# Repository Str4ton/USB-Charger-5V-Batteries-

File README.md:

# USB-Charger-5V-Batteries
A USB Charger for 5V Li-Ion batteries. It is designed to charge from a usb port, or something that will give 5V, 0.5A.

The circuit has a few protection circuits:
- A current limiter circuit so that the battery charges safely.
- A reverse polarity protection in case the battery is plugged in backwards that will not allow the circuit to start.
- A circuit that will stop the charging once it's done.

The PIC18 is used to monitor the charging and stop it when it's done and to light the 2 LEDs, one for when the charging is in process and the other for when it's done.\
The PIC18 is utilised more for convenience as the entire circuit could have been fully analog.

The schematics can be found in the [Charger USB.pdf](https://github.com/Str4ton/USB-Charger-5V-Batteries-/blob/main/Charger%20USB.pdf) file.

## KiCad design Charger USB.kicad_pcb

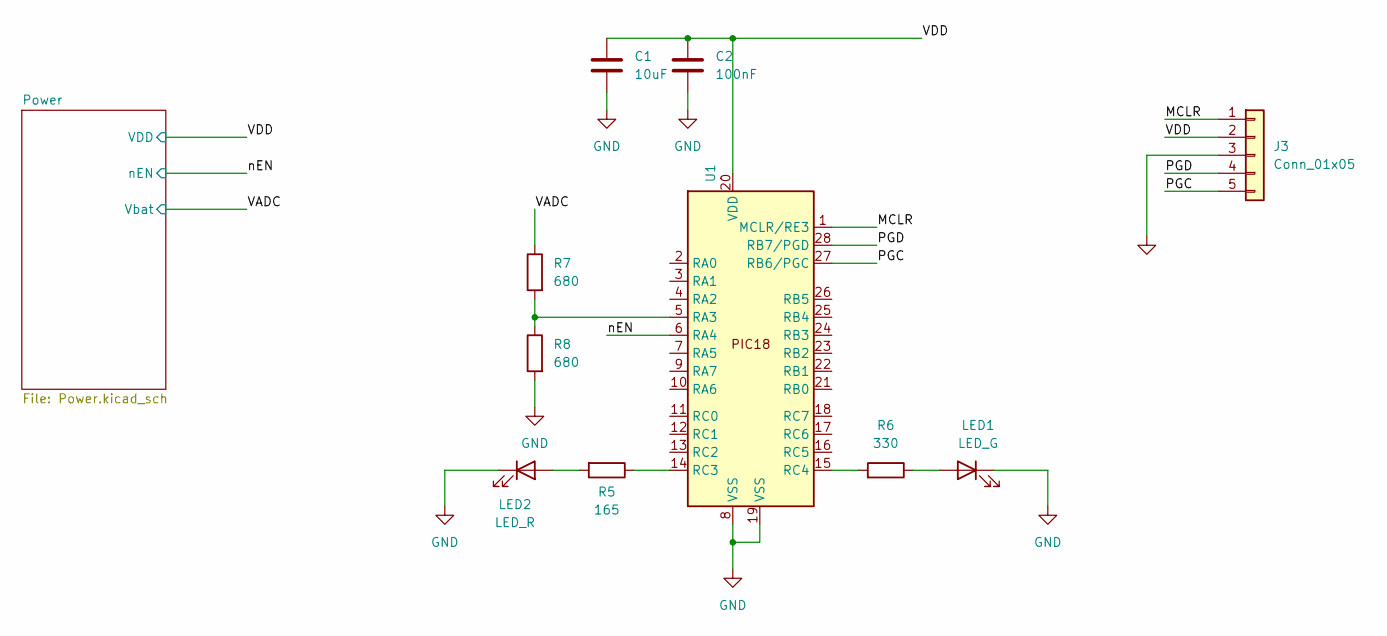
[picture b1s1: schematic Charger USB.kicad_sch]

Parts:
C1: 10uF; C_0805_2012Metric; Part# CL21A106KPFNNNE
C2: 100nF; C_0603_1608Metric; Part# 0402ZD104KAT2A
J3: Conn_01x05; PinSocket_1x05_P2.54mm_Vertical
LED1: LED_G; LED_D5.0mm; Part# LTL-307G
LED2: LED_R; LED_D5.0mm; Part# FYL-5013SRD1C
R5: 165; R_0805_2012Metric; Part# RC0805FR-07165RL
R6: 330; R_0603_1608Metric; Part# 0603SAF3300T5E
R7, R8: 680; R_1206_3216Metric; Part# 1206S4F1100T5E
U1: SOIC-28W_7.5x17.9mm_P1.27mm; Part# PIC18F26K42-I/SO

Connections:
/MCLR: J3.1, U1.1 (MCLR/RE3)
/PGC: J3.5, U1.27 (RB6/PGC)
/PGD: J3.4, U1.28 (RB7/PGD)
/VADC: R7.1; also elsewhere on the board
/VDD: C1.1, C2.1, J3.2, U1.20 (VDD); also elsewhere on the board
/nEN: U1.6 (RA4); also elsewhere on the board
GND: C1.2, C2.2, J3.3, LED1.1 (K), LED2.1 (K), R8.2, U1.8 (VSS), U1.19 (VSS); also elsewhere on the board
unnamed: LED1.2 (A), R6.1
unnamed: LED2.2 (A), R5.2
unnamed: R7.2, R8.1, U1.5 (RA3)
unnamed: R5.1, U1.14 (RC3)
unnamed: R6.2, U1.15 (RC4)

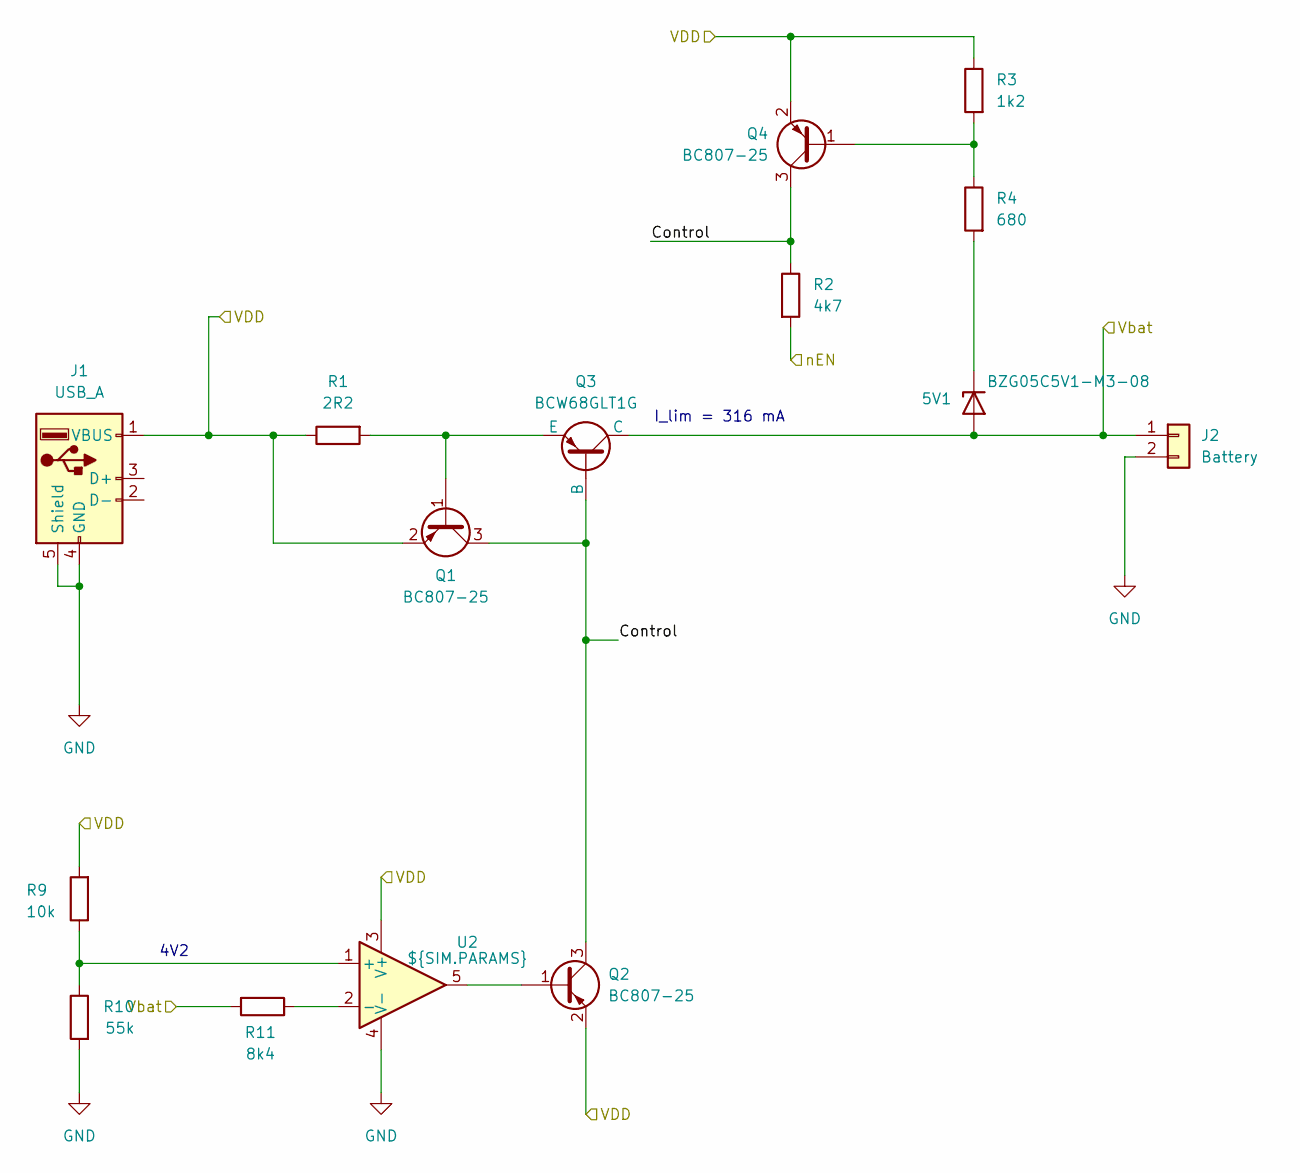
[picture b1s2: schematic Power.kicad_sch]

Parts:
BZG05C5V1-M3-08: 5V1; D_0201_0603Metric; Part# BZG05C5V1-M3-08
J1: USB_A; USB_A_Receptacle_GCT_USB1046
J2: Battery; PinHeader_1x02_P2.54mm_Vertical
Q1, Q2, Q4: BC807-25; SOT-23; Part# BC807-25
Q3: BCW68GLT1G; SOT-23; Part# BCW68GLT1G
R1: 2R2; R_0402_1005Metric; Part# ERJ2GEJ2R0X
R2: 4k7; R_0603_1608Metric; Part# RC0603FR-071KL
R3: 1k2; R_1206_3216Metric; Part# 1206S4F1100T5E
R4: 680; R_1206_3216Metric; Part# 1206S4F1100T5E
R9: 10k; R_0603_1608Metric; Part# RC0603FR-071KL
R10: 55k; R_0603_1608Metric; Part# RC0603FR-071KL
R11: 8k4; R_0805_2012Metric; Part# RC0603FR-071KL
U2: ${SIM.PARAMS}; SOT23-5L_1P75X3P05X0P95_STM

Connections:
/Power/Control: Q1.3 (C), Q2.3 (C), Q3.2 (B), Q4.3 (C), R2.1
/VADC: BZG05C5V1-M3-08.2 (A), J2.1, Q3.1 (C), R11.2; also elsewhere on the board
/VDD: J1.1 (VBUS), Q1.2 (E), Q2.2 (E), Q4.2 (E), R1.1, R3.1, R9.2, U2.3 (V+); also elsewhere on the board
/nEN: R2.2; also elsewhere on the board
GND: J1.4 (GND), J1.5 (Shield), J2.2, R10.2, U2.4 (V-); also elsewhere on the board
unnamed 8: BZG05C5V1-M3-08.1 (K), R4.2; also elsewhere on the board
unnamed: Q1.1 (B), Q3.3 (E), R1.2
unnamed: Q2.1 (B), U2.5
unnamed: Q4.1 (B), R3.2, R4.1
unnamed: R9.1, R10.1, U2.1 (+)
unnamed: R11.1, U2.2 (-)

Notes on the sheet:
4V2
I_lim = 316 mA

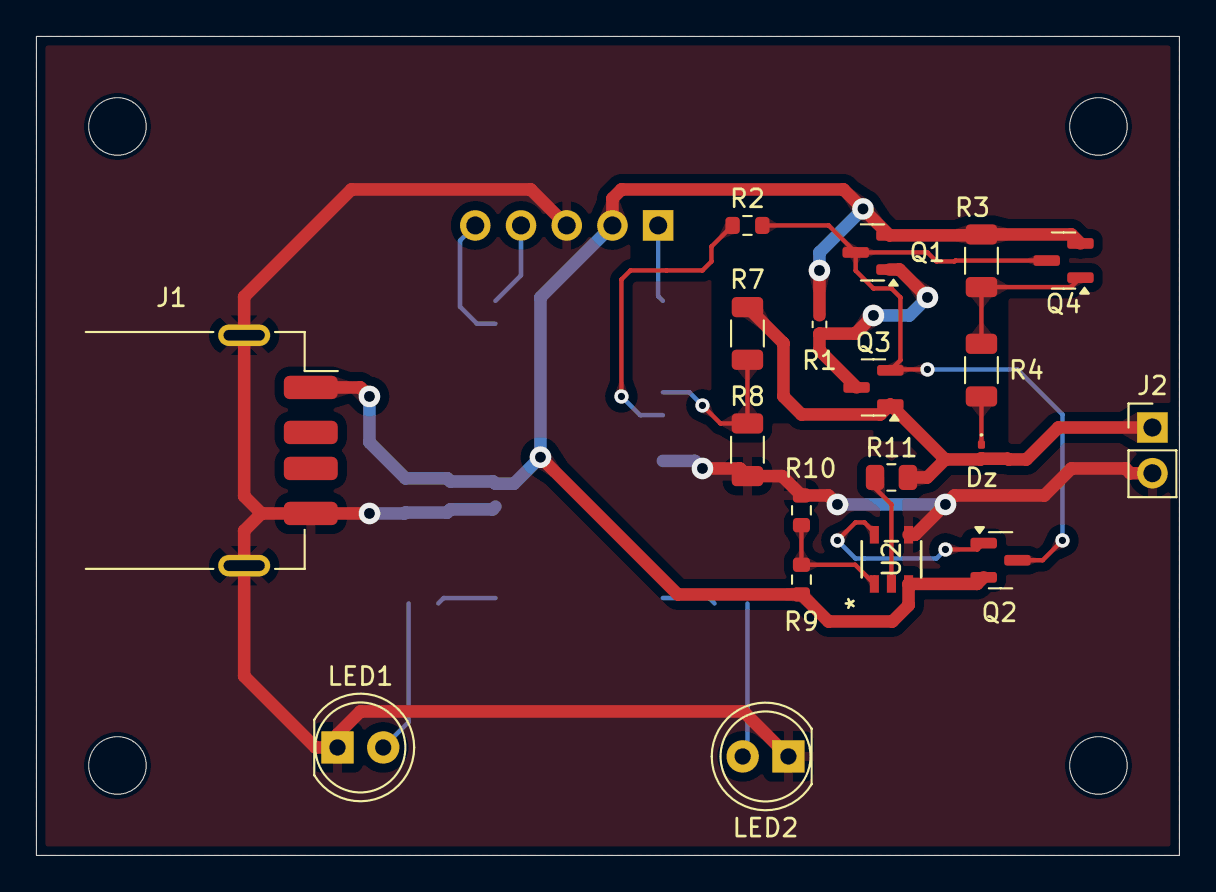
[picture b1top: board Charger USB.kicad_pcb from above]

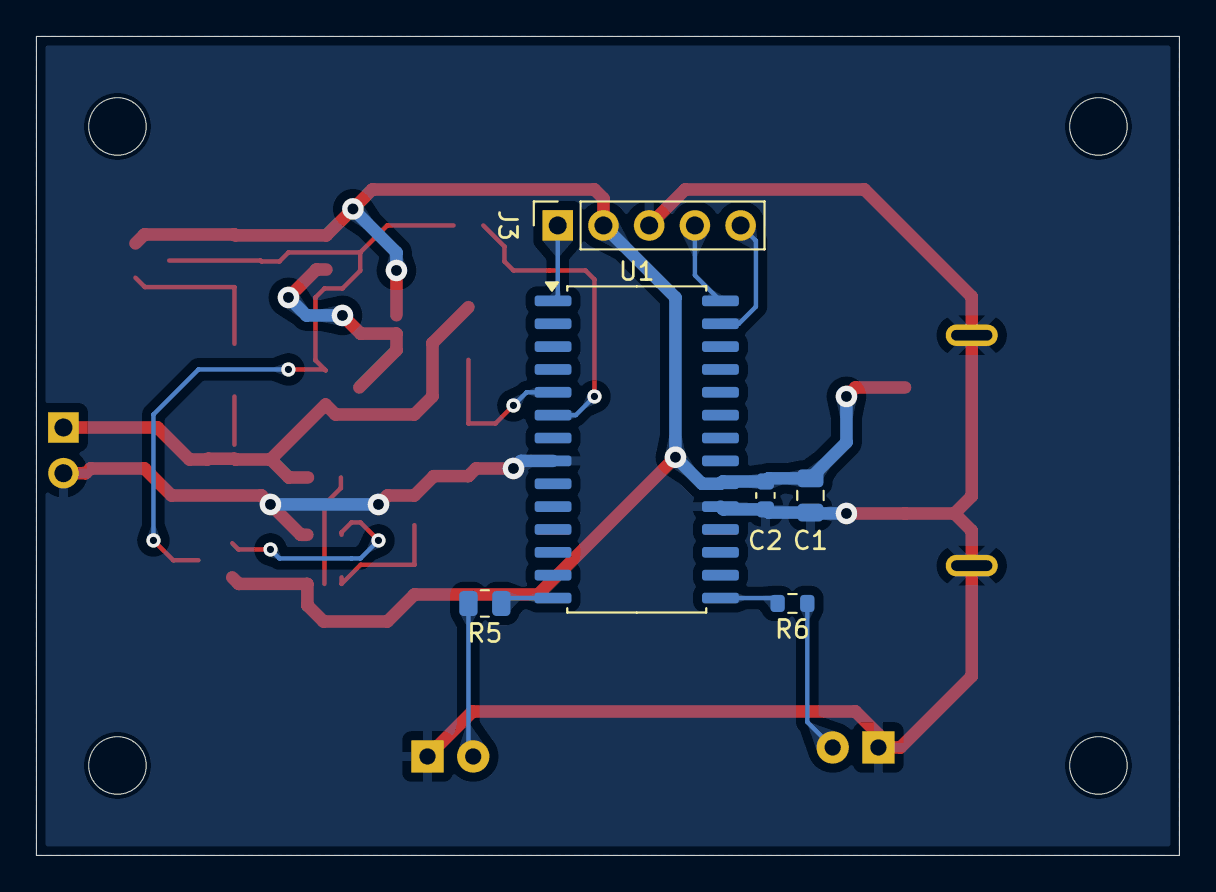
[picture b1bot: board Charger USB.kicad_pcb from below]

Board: 2 copper layers, 63.5 x 45.5 mm, 25 parts (6 on the bottom side), 19 nets.

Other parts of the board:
Dz: 5V1; D_0201_0603Metric

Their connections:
/VADC: Dz.2 (A); also elsewhere on the board
unnamed 8: Dz.1 (K); also elsewhere on the board

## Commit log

2025-07-27 Gerber
